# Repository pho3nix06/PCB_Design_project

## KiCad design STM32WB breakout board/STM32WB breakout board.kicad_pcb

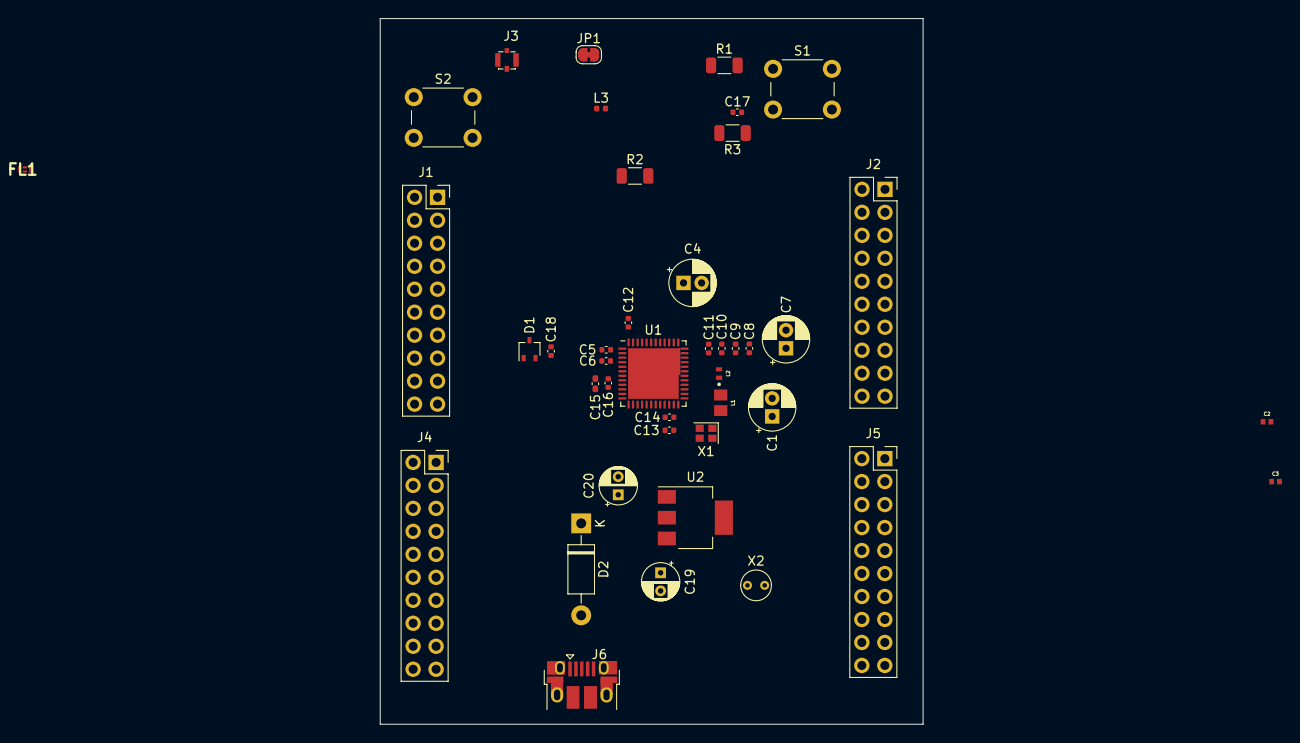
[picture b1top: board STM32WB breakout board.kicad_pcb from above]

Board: 2 copper layers, 60.0 x 78.0 mm, 42 parts (0 on the bottom side), 44 nets.

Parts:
C1, C4, C7: 4.7 uF; CP_Radial_D5.0mm_P2.00mm
C2: GRM1555C1HR80BA01D; CAPC1005X55N
C3: GRM1555C1HR30WA01D; CAPC1005X55N
C5, C6: 10 pF; C_0402_1005Metric
C8, C9, C10, C11, C12, C13, C17, C18: 100nF; C_0402_1005Metric
C14: 100 pF; C_0402_1005Metric
C15: 1 uF; C_0402_1005Metric_Pad0.74x0.62mm_HandSolder
C16: 10 nF; C_0402_1005Metric
C19, C20: 10uF; CP_Radial_D4.0mm_P2.00mm
D1: BAT54W; SOT-323_SC-70
D2: 1N5819; D_DO-41_SOD81_P10.16mm_Horizontal
FL1: DLF162500LT-5028A1; DLF162500LT5028A1
J1, J2, J4, J5: Conn_02x10_Counter_Clockwise; PinSocket_2x10_P2.54mm_Vertical
J3: RSP-122811-02; SAMTEC_RSP-122811-02
J6: USB_B_Micro; USB_Micro-B_Amphenol_10103594-0001LF_Horizontal
JP1: SolderJumper_2_Open; SolderJumper-2_P1.3mm_Bridged_RoundedPad1.0x1.5mm
L1: LQM21FN100M70L; INDC2012X145N
L2: LQG15WZ10NJ02D; INDC1006X60N
L3: LQG15HS2N7S02D; L_0402_1005Metric
R1: 1k; R_1206_3216Metric
R2: 10k; R_1206_3216Metric
R3: 100k; R_1206_3216Metric
S1: USER BUTTON; SW_PUSH_6mm
S2: RESET; SW_PUSH_6mm
U1: STM32WB15CCU6; QFN-48-1EP_7x7mm_P0.5mm_EP5.6x5.6mm
U2: LD1117S33TR_SOT223; SOT-223-3_TabPin2
X1: 32 MHz; Crystal_SMD_2016-4Pin_2.0x1.6mm
X2: 32.768 kHz; Crystal_Round_D3.0mm_Vertical

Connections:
3V3: C4.1, C7.1, C8.1, C9.1, C10.1, C11.1, C12.1, C13.1, C14.1, C15.1, C16.1, C20.1, J1.1, J4.1, JP1.1 (A), R1.2, U1.1 (VBAT), U1.8 (VDDA), U1.20 (VDD), U1.23 (VDDRF), U1.34 (VDDSMPS), U1.35 (VDD), U1.40 (VDD), U1.48 (VDD), U2.2 (VO)
/BOOT0: JP1.2 (B), R2.2, U1.4 (PH3)
/LPUART_RX/PA3: J1.14, J4.14, U1.12 (PA3)
/LPUART_TX/PA2: J1.15, J4.15, U1.11 (PA2)
/MISO/PA6: J1.11, U1.15 (PA6)
/MOSI/PA5: J1.12, U1.14 (PA5)
/NRST: C18.1, D1.1 (A), S2.1 (NO_1), U1.7 (NRST(PB11))
/NRST_Pin: D1.3 (K), J1.2, J4.2
/OSC32_IN: C5.1, U1.2 (PC14), X2.2
/OSC32_OUT: C6.1, U1.3 (PC15), X2.1
/OSC_IN: U1.25 (OSC_IN), X1.1
/OSC_OUT: U1.24 (OSC_OUT), X1.3
/PA0: J1.17, J4.17, U1.9 (PA0)
/PA1: J1.13, J4.13, J4.16
/PA7: J1.4, J4.4, U1.16 (PA7)
/PA8: J1.5, J4.5, U1.17 (PA8)
/PA9: J1.6, J4.6, U1.18 (PA9)
/PA10: J1.7, J4.7, U1.36 (PA10)
/PA11: J1.10, J4.10, U1.37 (PA11)
/PA12: J1.9, J4.9, U1.38 (PA12)
/PA15: J1.8, J4.8, U1.42 (PA15)
/PB2: J2.1, J5.1, U1.19 (PB2)
/PB3: J2.2, J5.2, U1.43 (PB3)
/PB4: J2.3, J5.3, U1.44 (PB4)
/PB5: J2.4, J5.4, U1.45 (PB5)
/PB6: J2.5, J5.5, U1.46 (PB6)
/PB7: J2.6, J5.6, U1.47 (PB7)
/PE4: J2.9, J5.9, U1.30 (PE4)
/RF1: C2.2, L3.1, U1.21 (RF1)
/SCK/PA1: J1.16, U1.10 (PA1)
/SCL/PB8: J2.7, J5.7, U1.5 (PB8)
/SDA/PB9: J2.8, J5.8, U1.6 (PB9)
/SWCLK: J1.18, J4.18, U1.41 (PA14)
/SWDIO: J1.19, J4.19, U1.39 (PA13)
/USR_BTN: C17.1, R3.2, U1.13 (PA4)
/VFBSMPS: C1.1, L1.2, U1.31 (VFBSMPS)
/VLXSMPS: L2.1, U1.33 (VLXSMPS)
GND: C1.2, C2.1, C3.1, C4.2, C5.2, C6.2, C7.2, C8.2, C9.2, C10.2, C11.2, C12.2, C13.2, C14.2, C15.2, C16.2, C17.2, C18.2, C19.2, C20.2, FL1.2 (GND_1), FL1.4 (GND_2), J1.3, J1.20, J3.2 (GND), J3.3 (GND), J3.4 (GND), J4.3, J4.20, J6.5 (GND), J6.6 (Shield), R2.1, R3.1, U1.22 (VSSRF), U1.32 (VSSSMPS), U1.49 (VSS), U2.1 (GND), X1.2, X1.4
unnamed: D2.2 (A), J6.1 (VBUS)
unnamed: C19.1, D2.1 (K), U2.3 (VI)
unnamed: C3.2, FL1.1 (IN), L3.2
unnamed: FL1.3 (OUT), J3.1 (SIGNAL)
unnamed: L1.1, L2.2
unnamed: R1.1, S1.2 (NO_2)

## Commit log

2023-12-14 Temp
2023-12-21 Switch updated
2023-12-23 Pinout updated
2023-12-24 PCB layout updated
2023-12-24 PCB layout and footprint updated
2023-12-24 PCB SMPS section inductors updated
2023-12-24 USB excluded
2023-12-24 PCB button updated
2023-12-25 Regulator section updating
2023-12-26 SMD resistors updated, some issue with inductor footprint
2023-12-26 L3 footprint updated
2023-12-27 AMS1117 updated
2023-12-27 USB added
2023-12-28 pcb updated
2023-12-31 MCU Symbol updated
2024-01-01 schematic updated
2024-01-06 Jumper pad updated
2024-01-07 LSE footprint updated
2024-01-09 STEP file added
